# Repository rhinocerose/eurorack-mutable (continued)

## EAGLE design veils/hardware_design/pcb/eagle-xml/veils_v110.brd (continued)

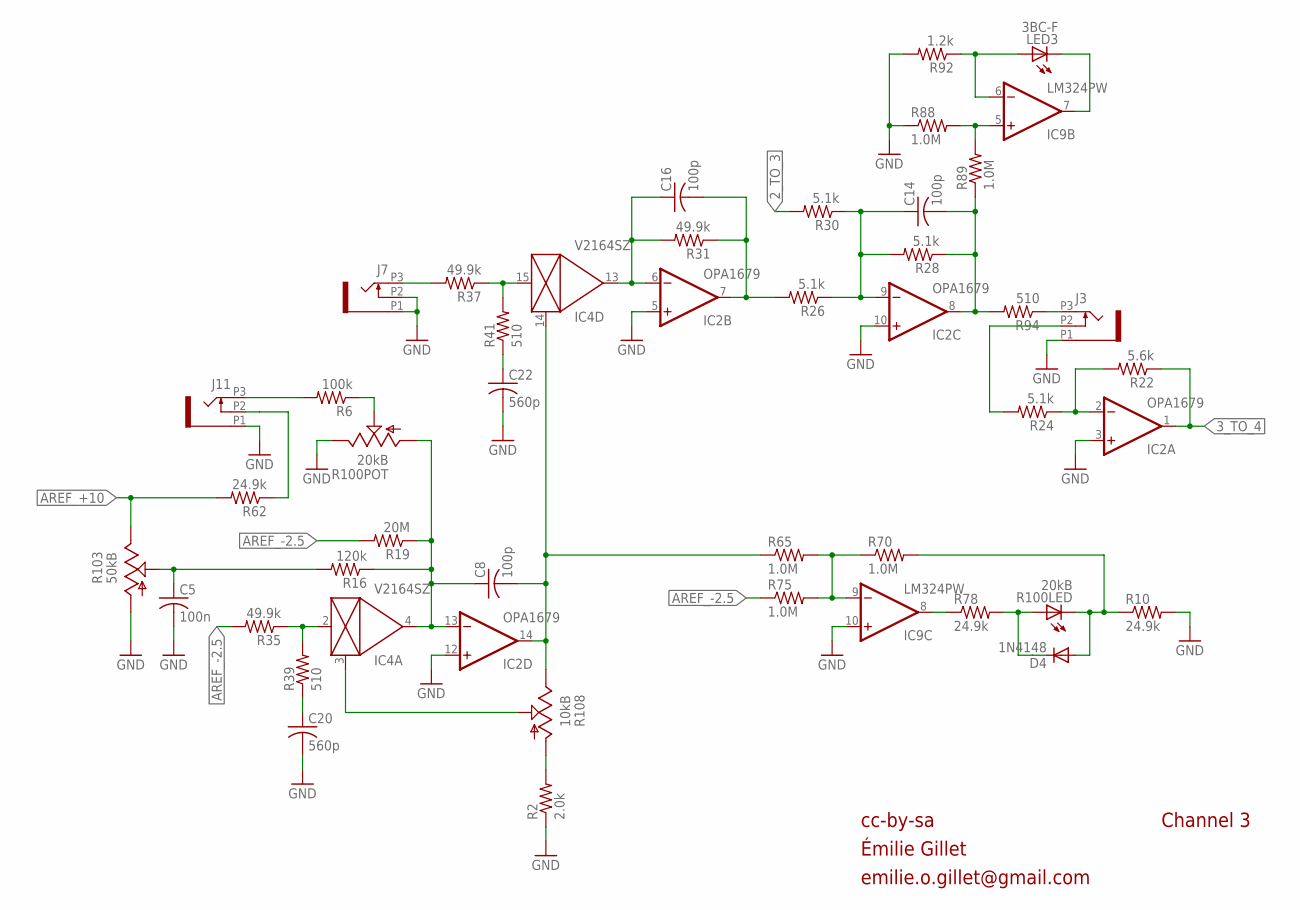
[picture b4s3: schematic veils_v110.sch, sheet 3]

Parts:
C5: 100n; C0402
C8, C14, C16: 100p; C0402
C20, C22: 560p; C0402
D4: 1N4148; SOD523
IC2: OPA1679; TSSOP14_065
IC4: V2164SZ; SOIC16N
IC9: LM324PW; TSSOP14_065
J3, J7, J11: PJ301_THONKICONNTME; WQP_PJ_301M_TME
LED3: 3BC-F; LED3MM
R2: 2.0k; R0402
R6: 100k; R0402
R10, R62, R78: 24.9k; R0402
R16: 120k; R0402
R19: 20M; R0402
R22: 5.6k; R0402
R24, R26, R28, R30: 5.1k; R0402
R31, R35, R37: 49.9k; R0402
R39, R41: 510; R0402
R65, R70, R75, R88, R89: 1.0M; R0402
R92: 1.2k; R0402
R94: 510; R0603
R100: 20kB; BOURNS_SLIDER
R103: 50kB; ALPS_POT_NARROW
R108: 10kB; ALPS_POT_NARROW

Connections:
2_TO_3: R30.2; also elsewhere on the board
3_TO_4: IC2.1 (OUT), R22.1; also elsewhere on the board
AREF_+10: R62.2, R103.P$1 (E); also elsewhere on the board
AREF_-2.5: R19.2, R35.2, R75.1; also elsewhere on the board
FOO2: IC4.2 (IN), R35.1, R39.2
GND: C5.2, C20.2, C22.2, IC2.3 (+IN), IC2.5 (+IN), IC2.10 (+IN), IC2.12 (+IN), IC9.10 (+IN), J3.P1 (1), J7.P1 (1), J7.P2 (2), J11.P1 (1), R2.1, R10.2, R88.1, R92.2, R100.3 (E), R103.P$3 (A); also elsewhere on the board
unnamed: IC9.5 (+IN), R88.2, R89.2
unnamed: J3.P3 (3), R94.1
unnamed: IC4.3 (CTRL), R108.P$2 (S)
unnamed: R2.2, R108.P$3 (A)
unnamed: J11.P3 (3), R6.2
unnamed: C22.1, R41.1
unnamed: IC4.15 (IN), R37.1, R41.2
unnamed: C14.1, IC2.9 (-IN), R26.1, R28.2, R30.1
unnamed: J7.P3 (3), R37.2
unnamed: C16.1, IC2.6 (-IN), IC4.13 (OUT), R31.2
unnamed: IC9.7 (OUT), LED3.K (C)
unnamed: IC9.6 (-IN), LED3.A, R92.1
unnamed: IC2.2 (-IN), R22.2, R24.1
unnamed: J3.P2 (2), R24.2
unnamed: C20.1, R39.1
unnamed: R6.1, R100.2 (S)
unnamed: C8.1, IC2.13 (-IN), IC4.4 (OUT), R16.1, R19.1, R100.1 (A)
unnamed: IC9.8 (OUT), R78.1
unnamed: D4.A, R10.1, R70.2, R100.E (C)
unnamed: IC9.9 (-IN), R65.2, R70.1, R75.2
unnamed: C8.2, IC2.14 (OUT), IC4.14 (CTRL), R65.1, R108.P$1 (E)
unnamed: J11.P2 (2), R62.1
unnamed: C5.1, R16.2, R103.P$2 (S)
unnamed: C16.2, IC2.7 (OUT), R26.2, R31.1
OUT3: C14.2, IC2.8 (OUT), R28.1, R89.1, R94.2
PROT3: D4.C, R78.2, R100.B (A)

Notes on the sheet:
cc-by-sa
Channel 3
Émilie Gillet
emilie.o.gillet@gmail.com

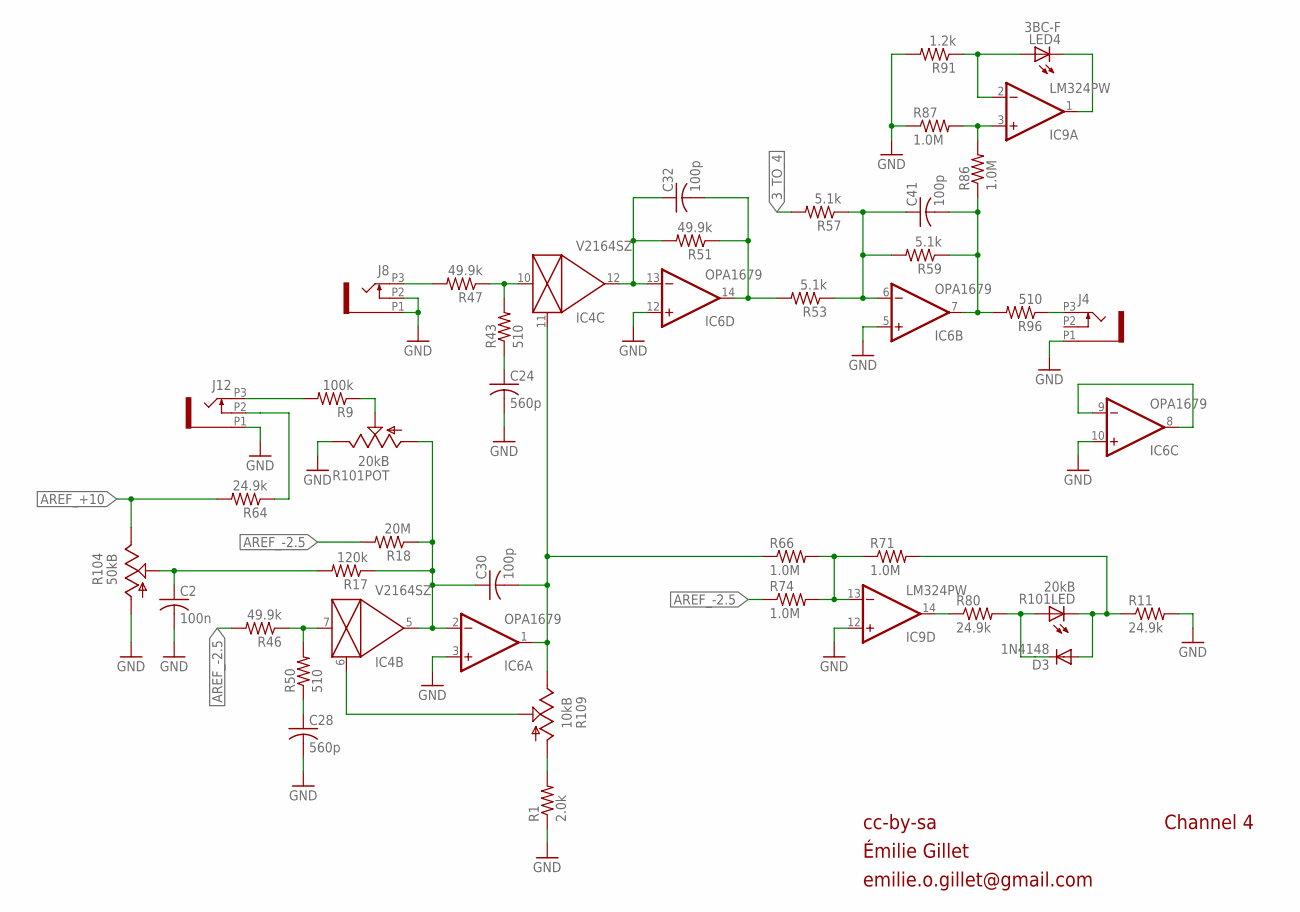
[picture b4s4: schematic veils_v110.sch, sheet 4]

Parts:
C2: 100n; C0402
C24, C28: 560p; C0402
C30, C32, C41: 100p; C0402
D3: 1N4148; SOD523
IC4: V2164SZ; SOIC16N
IC6: OPA1679; TSSOP14_065
IC9: LM324PW; TSSOP14_065
J4, J8, J12: PJ301_THONKICONNTME; WQP_PJ_301M_TME
LED4: 3BC-F; LED3MM
R1: 2.0k; R0402
R9: 100k; R0402
R11, R64, R80: 24.9k; R0402
R17: 120k; R0402
R18: 20M; R0402
R43, R50: 510; R0402
R46, R47, R51: 49.9k; R0402
R53, R57, R59: 5.1k; R0402
R66, R71, R74, R86, R87: 1.0M; R0402
R91: 1.2k; R0402
R96: 510; R0603
R101: 20kB; BOURNS_SLIDER
R104: 50kB; ALPS_POT_NARROW
R109: 10kB; ALPS_POT_NARROW

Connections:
3_TO_4: R57.2; also elsewhere on the board
AREF_+10: R64.2, R104.P$1 (E); also elsewhere on the board
AREF_-2.5: R18.2, R46.2, R74.1; also elsewhere on the board
FOO3: IC4.7 (IN), R46.1, R50.2
GND: C2.2, C24.2, C28.2, IC6.3 (+IN), IC6.5 (+IN), IC6.10 (+IN), IC6.12 (+IN), IC9.12 (+IN), J4.P1 (1), J8.P1 (1), J8.P2 (2), J12.P1 (1), R1.1, R11.2, R87.1, R91.2, R101.3 (E), R104.P$3 (A); also elsewhere on the board
unnamed: IC6.8 (OUT), IC6.9 (-IN)
unnamed: IC9.3 (+IN), R86.2, R87.2
unnamed: IC4.6 (CTRL), R109.P$2 (S)
unnamed: J12.P2 (2), R64.1
unnamed: R1.2, R109.P$3 (A)
unnamed: J12.P3 (3), R9.2
unnamed: C32.1, IC4.12 (OUT), IC6.13 (-IN), R51.2
unnamed: J8.P3 (3), R47.2
unnamed: R9.1, R101.2 (S)
unnamed: J4.P3 (3), R96.1
unnamed: C24.1, R43.1
unnamed: IC4.10 (IN), R43.2, R47.1
unnamed: C41.1, IC6.6 (-IN), R53.1, R57.1, R59.2
unnamed: IC9.1 (OUT), LED4.K (C)
unnamed: IC9.2 (-IN), LED4.A, R91.1
unnamed: IC9.14 (OUT), R80.1
unnamed: C32.2, IC6.14 (OUT), R51.1, R53.2
unnamed: C28.1, R50.1
unnamed: C30.1, IC4.5 (OUT), IC6.2 (-IN), R17.1, R18.1, R101.1 (A)
unnamed: D3.A, R11.1, R71.2, R101.E (C)
unnamed: IC9.13 (-IN), R66.2, R71.1, R74.2
unnamed: C30.2, IC4.11 (CTRL), IC6.1 (OUT), R66.1, R109.P$1 (E)
unnamed: C2.1, R17.2, R104.P$2 (S)
OUT4: C41.2, IC6.7 (OUT), R59.1, R86.1, R96.2
PROT4: D3.C, R80.2, R101.B (A)

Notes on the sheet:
cc-by-sa
Channel 4
Émilie Gillet
emilie.o.gillet@gmail.com

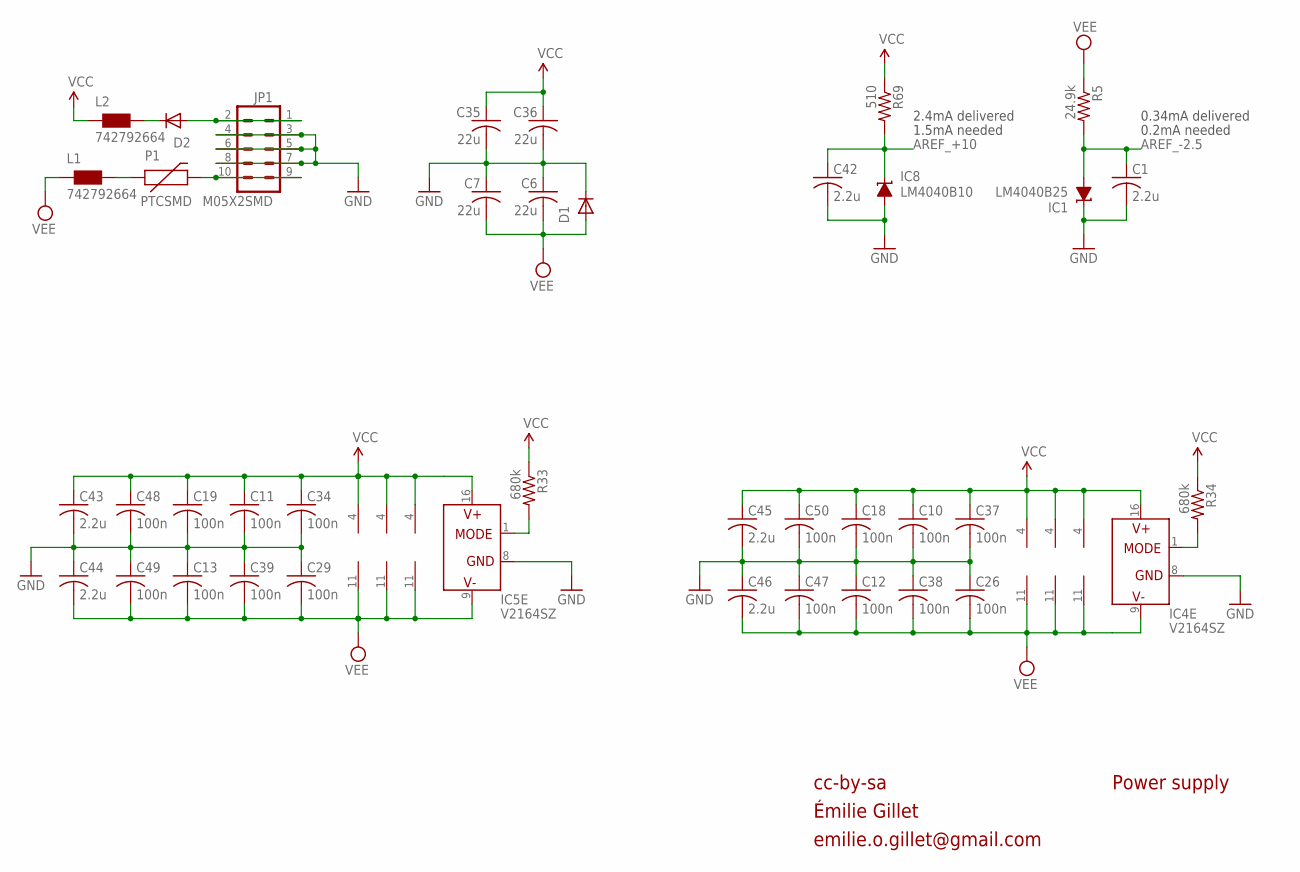
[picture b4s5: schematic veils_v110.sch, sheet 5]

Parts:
C1, C42, C43, C44, C45, C46: 2.2u; C0603
C6, C7, C35, C36: 22u; C1206
C10, C11, C12, C13, C18, C19, C26, C29, C34, C37, C38, C39, C47, C48, C49, C50: 100n; C0402
D1, D2: 1N5819HW; SOD123
IC1: LM4040B25; DBZ_R-PDSO-G3
IC2, IC3, IC6, IC7: OPA1679; TSSOP14_065
IC4, IC5: V2164SZ; SOIC16N
IC8: LM4040B10; DBZ_R-PDSO-G3
IC9, IC10: LM324PW; TSSOP14_065
JP1: M05X2SMD; 2X5-SMD
L1, L2: 742792664; 0603
P1: PTCSMD; PTC-1206
R5: 24.9k; R0402
R33, R34: 680k; R0402
R69: 510; R0402

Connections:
AREF_+10: C42.1, IC8.1 (C), R69.2; also elsewhere on the board
AREF_-2.5: C1.1, IC1.2 (A), R5.2; also elsewhere on the board
GND: C1.2, C6.1, C7.1, C10.2, C11.2, C12.1, C13.1, C18.2, C19.2, C26.1, C29.1, C34.2, C35.2, C36.2, C37.2, C38.1, C39.1, C42.2, C43.2, C44.1, C45.2, C46.1, C47.1, C48.2, C49.1, C50.2, D1.C, IC1.1 (C), IC4.8 (GND), IC5.8 (GND), IC8.2 (A), JP1.3, JP1.4, JP1.5, JP1.6, JP1.7, JP1.8; also elsewhere on the board
unnamed: D2.A, JP1.1, JP1.2
unnamed: JP1.9, JP1.10, P1.2
unnamed: L1.2, P1.1
unnamed: D2.C, L2.2
unnamed: IC5.1 (MODE), R33.2
unnamed: IC4.1 (MODE), R34.2
VCC: C10.1, C11.1, C18.1, C19.1, C34.1, C35.1, C36.1, C37.1, C43.1, C45.1, C48.1, C50.1, IC2.4 (V+), IC3.4 (V+), IC4.16 (V+), IC5.16 (V+), IC6.4 (V+), IC7.4 (V+), IC9.4 (V+), IC10.4 (V+), L2.1, R33.1, R34.1, R69.1
VEE: C6.2, C7.2, C12.2, C13.2, C26.2, C29.2, C38.2, C39.2, C44.2, C46.2, C47.2, C49.2, D1.A, IC2.11 (V-), IC3.11 (V-), IC4.9 (V-), IC5.9 (V-), IC6.11 (V-), IC7.11 (V-), IC9.11 (V-), IC10.11 (V-), L1.1, R5.1

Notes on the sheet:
cc-by-sa
Power supply
0.34mA delivered
2.4mA delivered
0.2mA needed
1.5mA needed
Émilie Gillet
emilie.o.gillet@gmail.com

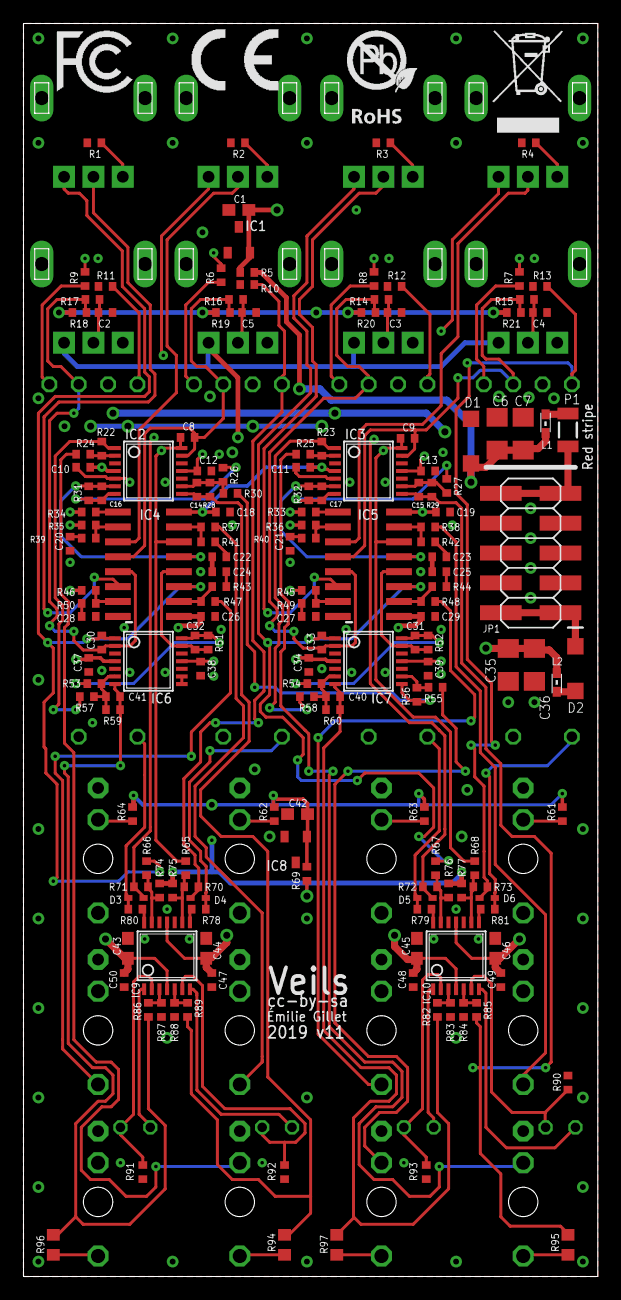
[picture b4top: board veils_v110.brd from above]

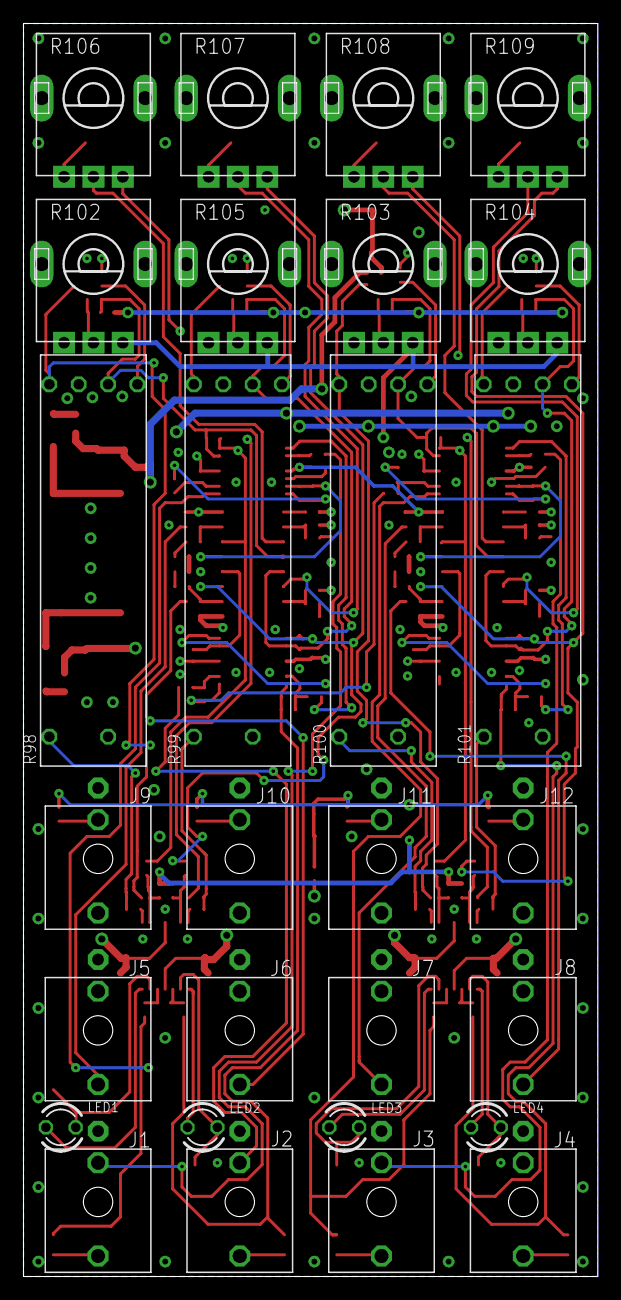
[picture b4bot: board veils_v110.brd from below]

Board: 4 copper layers, 48.9 x 106.7 mm, 199 parts (28 on the bottom side), 121 nets.

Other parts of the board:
U$1: CE_MEDIUM
U$2: FCC_MEDIUM
U$3: ROHS_LOGO
U$4: TRASHCAN_LOGO

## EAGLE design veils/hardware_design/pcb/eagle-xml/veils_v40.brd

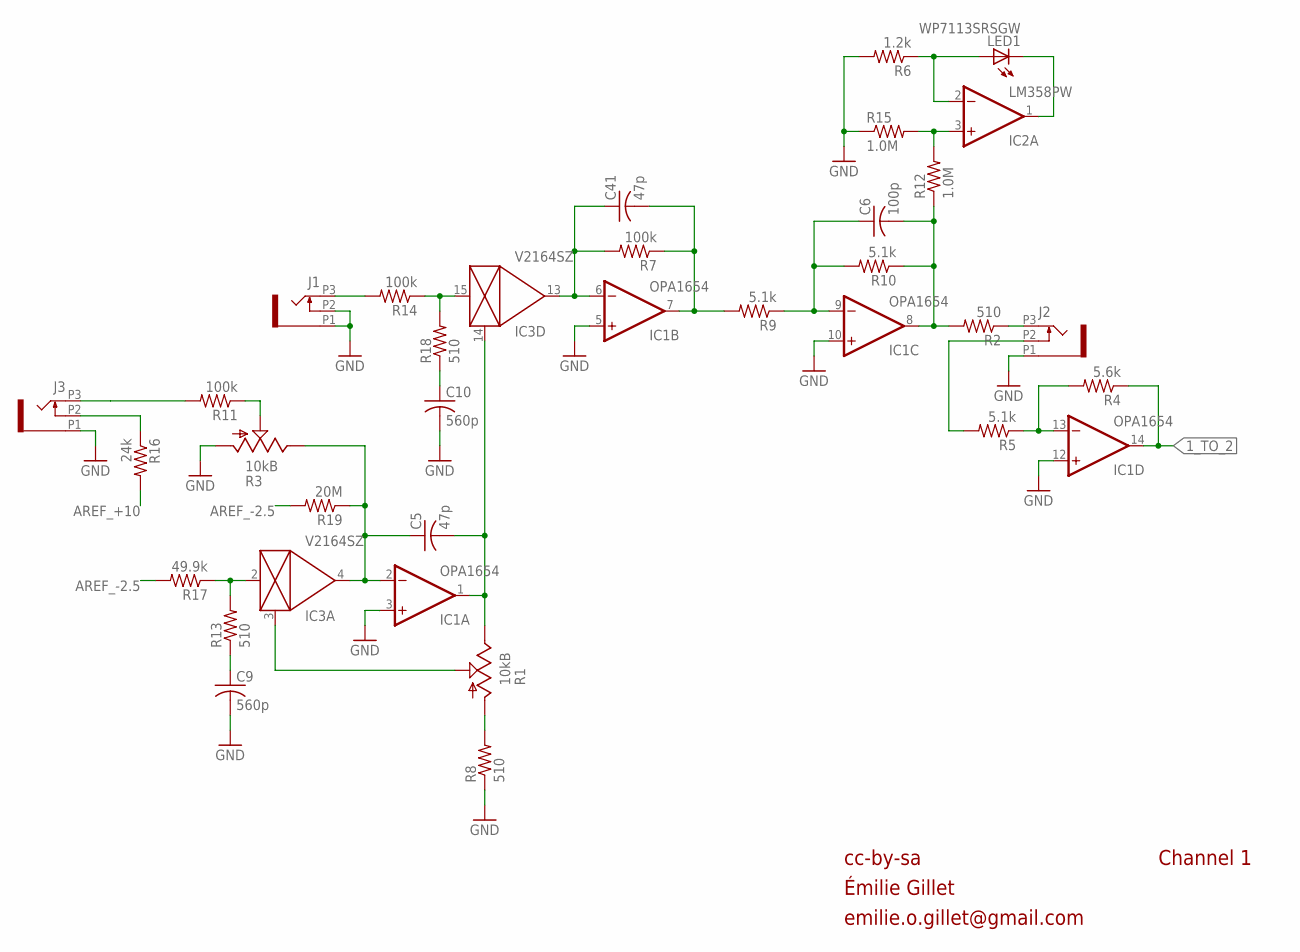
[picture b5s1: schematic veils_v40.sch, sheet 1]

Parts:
C5, C41: 47p; C0402
C6: 100p; C0402
C9, C10: 560p; C0402
IC1: OPA1654; TSSOP14
IC2: LM358PW; TSSOP8
IC3: V2164SZ; SOIC16N
J1, J2, J3: PJ301_THONKICONN6; WQP_PJ_301M6
LED1: WP7113SRSGW; LED5MM
R1: 10kB; ALPS_POT_VERTICAL
R2, R8, R13, R18: 510; R0402
R3: 10kB; ALPS_POT_VERTICAL_PS
R4: 5.6k; R0402
R5, R9, R10: 5.1k; R0402
R6: 1.2k; R0402
R7, R11, R14: 100k; R0402
R12, R15: 1.0M; R0402
R16: 24k; R0402
R17: 49.9k; R0402
R19: 20M; R0402

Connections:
1_TO_2: IC1.14 (OUT), R4.1; also elsewhere on the board
AREF_+10: R16.2; also elsewhere on the board
AREF_-2.5: R17.2, R19.2; also elsewhere on the board
CV_IN_1: J3.P3 (3), R11.2
FOO: IC3.2 (IN), R13.2, R17.1
GND: C9.2, C10.2, IC1.3 (+IN), IC1.5 (+IN), IC1.10 (+IN), IC1.12 (+IN), J1.P1 (1), J1.P2 (2), J2.P1 (1), J3.P1 (1), R3.P$3 (A), R6.2, R8.1, R15.1; also elsewhere on the board
unnamed: IC2.3 (+IN), R12.2, R15.2
unnamed: J2.P3 (3), R2.1
unnamed: IC3.3 (CTRL), R1.P$2 (S)
unnamed: C6.1, IC1.9 (-IN), R9.1, R10.2
unnamed: R3.P$2 (S), R11.1
unnamed: R1.P$3 (A), R8.2
unnamed: IC2.1 (OUT), LED1.K (C)
unnamed: IC2.2 (-IN), LED1.A, R6.1
unnamed: C9.1, R13.1
unnamed: J3.P2 (2), R16.1
unnamed: IC1.13 (-IN), R4.2, R5.1
unnamed: J2.P2 (2), R5.2
unnamed: C10.1, R18.1
unnamed: C5.1, IC1.2 (-IN), IC3.4 (OUT), R3.P$1 (E), R19.1
unnamed: J1.P3 (3), R14.2
unnamed: IC3.15 (IN), R14.1, R18.2
unnamed: C5.2, IC1.1 (OUT), IC3.14 (CTRL), R1.P$1 (E)
unnamed: C41.1, IC1.6 (-IN), IC3.13 (OUT), R7.2
unnamed: C41.2, IC1.7 (OUT), R7.1, R9.2
OUT1: C6.2, IC1.8 (OUT), R2.2, R10.1, R12.1

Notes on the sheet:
cc-by-sa
Channel 1
Émilie Gillet
emilie.o.gillet@gmail.com

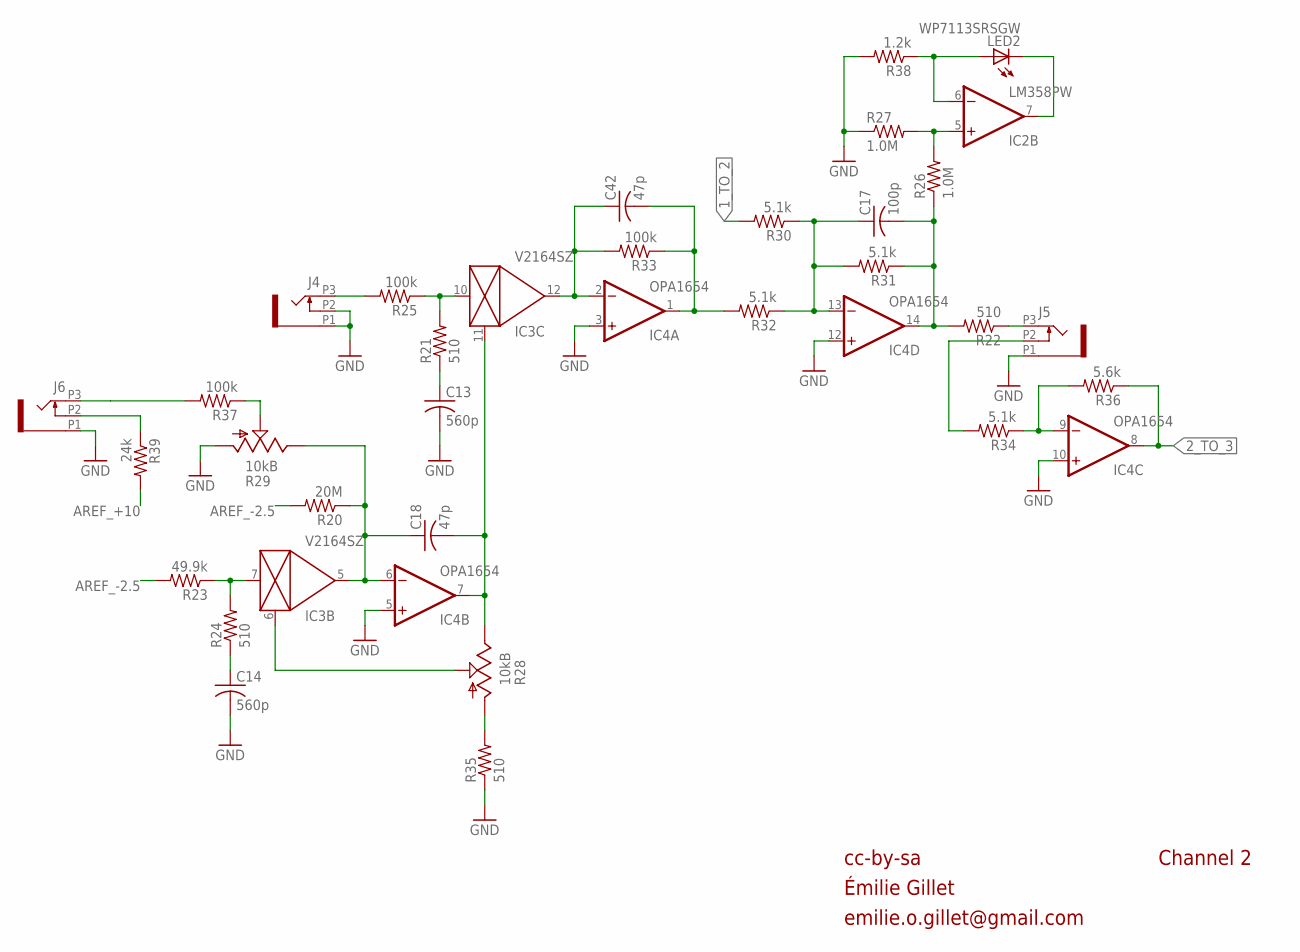
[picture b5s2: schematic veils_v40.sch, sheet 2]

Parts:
C13, C14: 560p; C0402
C17: 100p; C0402
C18, C42: 47p; C0402
IC2: LM358PW; TSSOP8
IC3: V2164SZ; SOIC16N
IC4: OPA1654; TSSOP14
J4, J5, J6: PJ301_THONKICONN6; WQP_PJ_301M6
LED2: WP7113SRSGW; LED5MM
R20: 20M; R0402
R21, R22, R24, R35: 510; R0402
R23: 49.9k; R0402
R25, R33, R37: 100k; R0402
R26, R27: 1.0M; R0402
R28: 10kB; ALPS_POT_VERTICAL
R29: 10kB; ALPS_POT_VERTICAL_PS
R30, R31, R32, R34: 5.1k; R0402
R36: 5.6k; R0402
R38: 1.2k; R0402
R39: 24k; R0402

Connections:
1_TO_2: R30.2; also elsewhere on the board
2_TO_3: IC4.8 (OUT), R36.1; also elsewhere on the board
AREF_+10: R39.2; also elsewhere on the board
AREF_-2.5: R20.2, R23.2; also elsewhere on the board
FOO1: IC3.7 (IN), R23.1, R24.2
GND: C13.2, C14.2, IC4.3 (+IN), IC4.5 (+IN), IC4.10 (+IN), IC4.12 (+IN), J4.P1 (1), J4.P2 (2), J5.P1 (1), J6.P1 (1), R27.1, R29.P$3 (A), R35.1, R38.2; also elsewhere on the board
unnamed: J4.P3 (3), R25.2
unnamed: IC2.5 (+IN), R26.2, R27.2
unnamed: J5.P3 (3), R22.1
unnamed: C13.1, R21.1
unnamed: IC3.10 (IN), R21.2, R25.1
unnamed: IC3.6 (CTRL), R28.P$2 (S)
unnamed: C17.1, IC4.13 (-IN), R30.1, R31.2, R32.1
unnamed: C18.2, IC3.11 (CTRL), IC4.7 (OUT), R28.P$1 (E)
unnamed: R28.P$3 (A), R35.2
unnamed: IC2.7 (OUT), LED2.K (C)
unnamed: IC2.6 (-IN), LED2.A, R38.1
unnamed: IC4.9 (-IN), R34.1, R36.2
unnamed: J5.P2 (2), R34.2
unnamed: C42.2, IC4.1 (OUT), R32.2, R33.1
unnamed: R29.P$2 (S), R37.1
unnamed: C14.1, R24.1
unnamed: C18.1, IC3.5 (OUT), IC4.6 (-IN), R20.1, R29.P$1 (E)
unnamed: J6.P3 (3), R37.2
unnamed: C42.1, IC3.12 (OUT), IC4.2 (-IN), R33.2
unnamed: J6.P2 (2), R39.1
OUT2: C17.2, IC4.14 (OUT), R22.2, R26.1, R31.1

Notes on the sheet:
cc-by-sa
Channel 2
Émilie Gillet
emilie.o.gillet@gmail.com

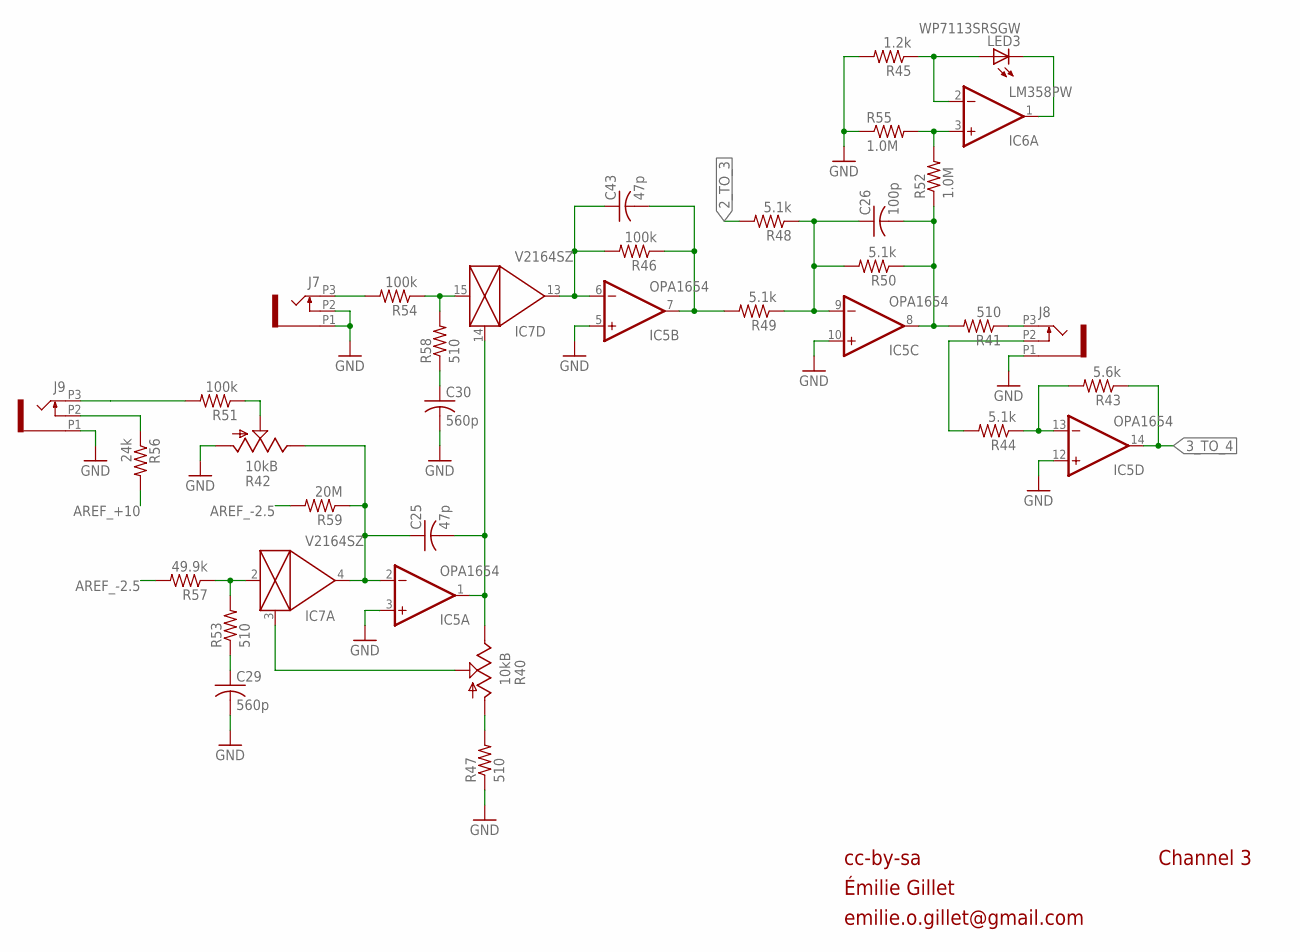
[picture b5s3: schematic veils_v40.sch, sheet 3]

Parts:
C25, C43: 47p; C0402
C26: 100p; C0402
C29, C30: 560p; C0402
IC5: OPA1654; TSSOP14
IC6: LM358PW; TSSOP8
IC7: V2164SZ; SOIC16N
J7, J8, J9: PJ301_THONKICONN6; WQP_PJ_301M6
LED3: WP7113SRSGW; LED5MM
R40: 10kB; ALPS_POT_VERTICAL
R41, R47, R53, R58: 510; R0402
R42: 10kB; ALPS_POT_VERTICAL_PS
R43: 5.6k; R0402
R44, R48, R49, R50: 5.1k; R0402
R45: 1.2k; R0402
R46, R51, R54: 100k; R0402
R52, R55: 1.0M; R0402
R56: 24k; R0402
R57: 49.9k; R0402
R59: 20M; R0402

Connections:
2_TO_3: R48.2; also elsewhere on the board
3_TO_4: IC5.14 (OUT), R43.1; also elsewhere on the board
AREF_+10: R56.2; also elsewhere on the board
AREF_-2.5: R57.2, R59.2; also elsewhere on the board
FOO2: IC7.2 (IN), R53.2, R57.1
GND: C29.2, C30.2, IC5.3 (+IN), IC5.5 (+IN), IC5.10 (+IN), IC5.12 (+IN), J7.P1 (1), J7.P2 (2), J8.P1 (1), J9.P1 (1), R42.P$3 (A), R45.2, R47.1, R55.1; also elsewhere on the board
unnamed: IC6.3 (+IN), R52.2, R55.2
unnamed: J8.P3 (3), R41.1
unnamed: IC7.3 (CTRL), R40.P$2 (S)
unnamed: C25.2, IC5.1 (OUT), IC7.14 (CTRL), R40.P$1 (E)
unnamed: R40.P$3 (A), R47.2
unnamed: C30.1, R58.1
unnamed: IC7.15 (IN), R54.1, R58.2
unnamed: C26.1, IC5.9 (-IN), R48.1, R49.1, R50.2
unnamed: J9.P2 (2), R56.1
unnamed: J7.P3 (3), R54.2
unnamed: J9.P3 (3), R51.2
unnamed: C43.1, IC5.6 (-IN), IC7.13 (OUT), R46.2
unnamed: IC6.1 (OUT), LED3.K (C)
unnamed: IC6.2 (-IN), LED3.A, R45.1
unnamed: IC5.13 (-IN), R43.2, R44.1
unnamed: J8.P2 (2), R44.2
unnamed: C29.1, R53.1
unnamed: C25.1, IC5.2 (-IN), IC7.4 (OUT), R42.P$1 (E), R59.1
unnamed: R42.P$2 (S), R51.1
unnamed: C43.2, IC5.7 (OUT), R46.1, R49.2
OUT3: C26.2, IC5.8 (OUT), R41.2, R50.1, R52.1

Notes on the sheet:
cc-by-sa
Channel 3
Émilie Gillet
emilie.o.gillet@gmail.com

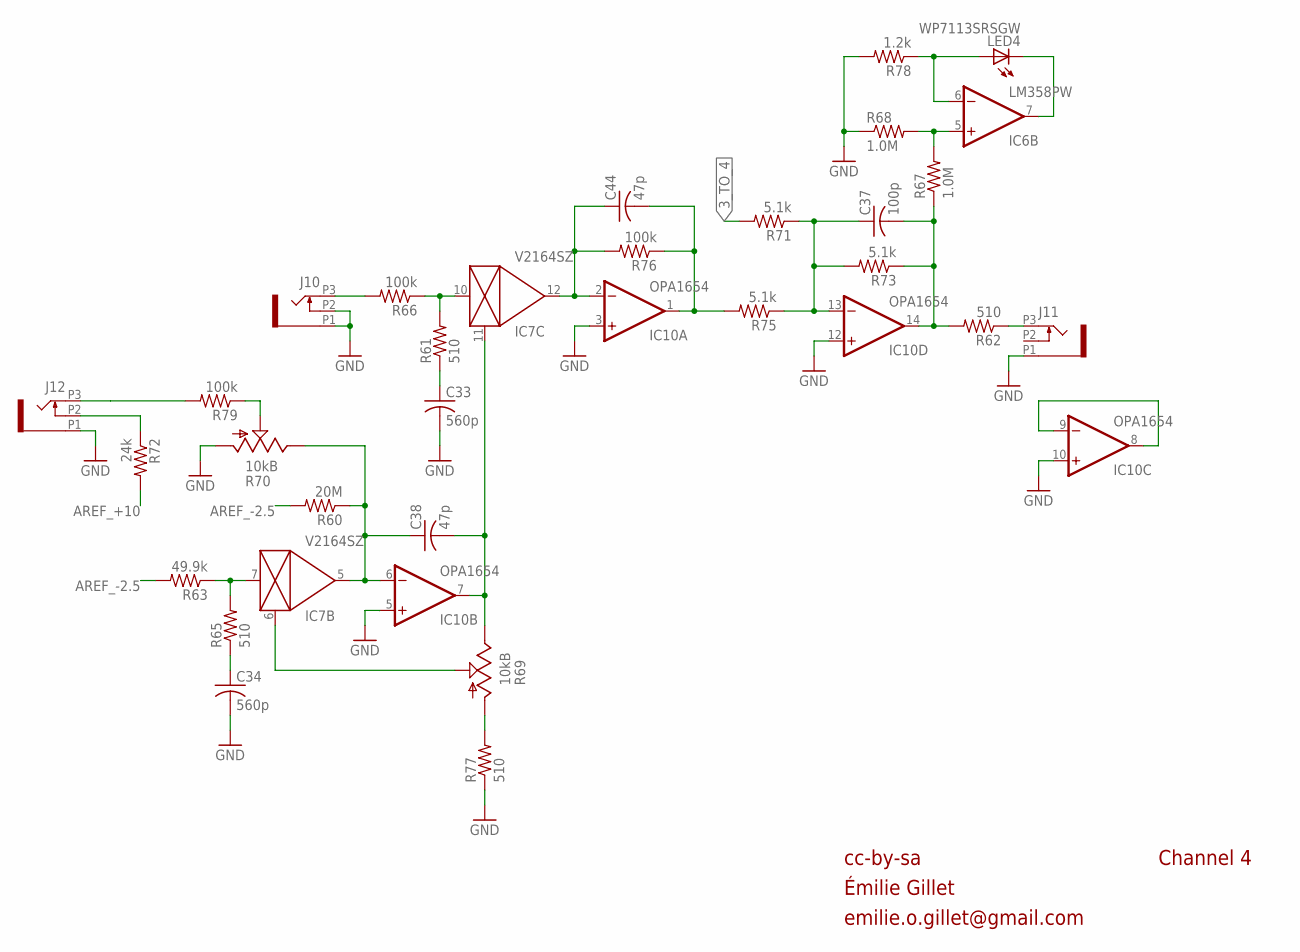
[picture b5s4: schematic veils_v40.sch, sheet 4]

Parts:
C33, C34: 560p; C0402
C37: 100p; C0402
C38, C44: 47p; C0402
IC6: LM358PW; TSSOP8
IC7: V2164SZ; SOIC16N
IC10: OPA1654; TSSOP14
J10, J11, J12: PJ301_THONKICONN6; WQP_PJ_301M6
LED4: WP7113SRSGW; LED5MM
R60: 20M; R0402
R61, R62, R65, R77: 510; R0402
R63: 49.9k; R0402
R66, R76, R79: 100k; R0402
R67, R68: 1.0M; R0402
R69: 10kB; ALPS_POT_VERTICAL
R70: 10kB; ALPS_POT_VERTICAL_PS
R71, R73, R75: 5.1k; R0402
R72: 24k; R0402
R78: 1.2k; R0402

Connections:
3_TO_4: R71.2; also elsewhere on the board
AREF_+10: R72.2; also elsewhere on the board
AREF_-2.5: R60.2, R63.2; also elsewhere on the board
FOO3: IC7.7 (IN), R63.1, R65.2
GND: C33.2, C34.2, IC10.3 (+IN), IC10.5 (+IN), IC10.10 (+IN), IC10.12 (+IN), J10.P1 (1), J10.P2 (2), J11.P1 (1), J12.P1 (1), R68.1, R70.P$3 (A), R77.1, R78.2; also elsewhere on the board
unnamed: IC10.8 (OUT), IC10.9 (-IN)
unnamed: IC6.5 (+IN), R67.2, R68.2
unnamed: C38.2, IC7.11 (CTRL), IC10.7 (OUT), R69.P$1 (E)
unnamed: IC7.6 (CTRL), R69.P$2 (S)
unnamed: R69.P$3 (A), R77.2
unnamed: C44.1, IC7.12 (OUT), IC10.2 (-IN), R76.2
unnamed: J10.P3 (3), R66.2
unnamed: J11.P3 (3), R62.1
unnamed: C33.1, R61.1
unnamed: IC7.10 (IN), R61.2, R66.1
unnamed: C37.1, IC10.13 (-IN), R71.1, R73.2, R75.1
unnamed: J12.P3 (3), R79.2
unnamed: IC6.7 (OUT), LED4.K (C)
unnamed: IC6.6 (-IN), LED4.A, R78.1
unnamed: C44.2, IC10.1 (OUT), R75.2, R76.1
unnamed: R70.P$2 (S), R79.1
unnamed: C34.1, R65.1
unnamed: C38.1, IC7.5 (OUT), IC10.6 (-IN), R60.1, R70.P$1 (E)
unnamed: J12.P2 (2), R72.1
OUT4: C37.2, IC10.14 (OUT), R62.2, R67.1, R73.1

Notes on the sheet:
cc-by-sa
Channel 4
Émilie Gillet
emilie.o.gillet@gmail.com

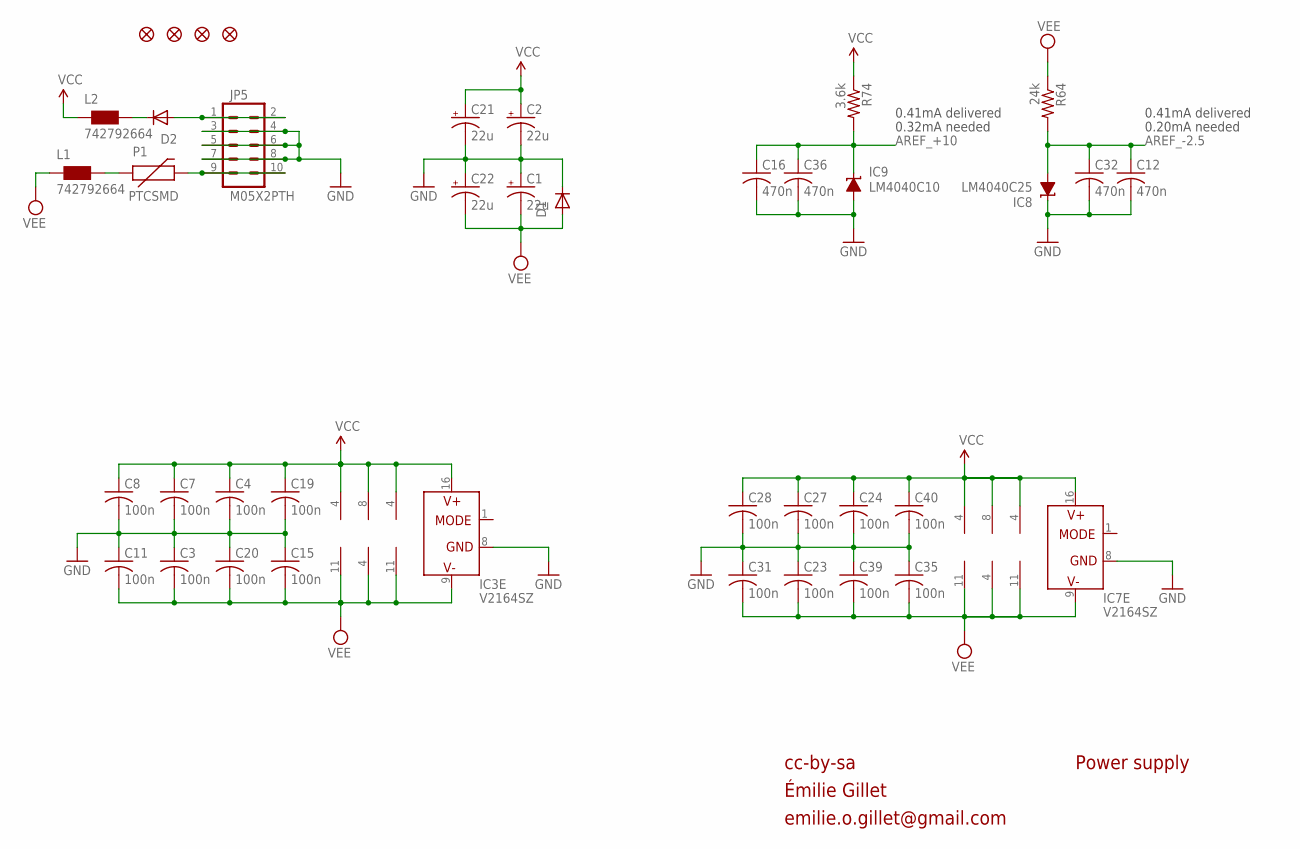
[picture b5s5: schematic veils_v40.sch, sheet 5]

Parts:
C1, C2, C21, C22: 22u; PANASONIC_B
C3, C4, C7, C8, C11, C15, C19, C20, C23, C24, C27, C28, C31, C35, C39, C40: 100n; C0402
C12, C16, C32, C36: 470n; C0402
D1, D2: 1N5819HW; SOD123
IC1, IC4, IC5, IC10: OPA1654; TSSOP14
IC2, IC6: LM358PW; TSSOP8
IC3, IC7: V2164SZ; SOIC16N
IC8: LM4040C25; DBZ_R-PDSO-G3
IC9: LM4040C10; DBZ_R-PDSO-G3
JP1, JP2, JP3, JP4: FIDUCIAL1X2; FIDUCIAL-1X2
JP5: M05X2PTH; AVR_ICSP
L1, L2: 742792664; 0603
P1: PTCSMD; PTC-1206
R64: 24k; R0402
R74: 3.6k; R0402

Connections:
AREF_+10: C16.1, C36.1, IC9.1 (C), R74.2; also elsewhere on the board
AREF_-2.5: C12.1, C32.1, IC8.2 (A), R64.2; also elsewhere on the board
GND: C1.+, C2.-, C3.1, C4.2, C7.2, C8.2, C11.1, C12.2, C15.1, C16.2, C19.2, C20.1, C21.-, C22.+, C23.1, C24.2, C27.2, C28.2, C31.1, C32.2, C35.1, C36.2, C39.1, C40.2, D1.C, IC3.8 (GND), IC7.8 (GND), IC8.1 (C), IC9.2 (A), JP5.3, JP5.4, JP5.5, JP5.6, JP5.7, JP5.8; also elsewhere on the board
unnamed: D2.A, JP5.1, JP5.2
unnamed: JP5.9, JP5.10, P1.2
unnamed: L1.2, P1.1
unnamed: D2.C, L2.2
VCC: C2.+, C4.1, C7.1, C8.1, C19.1, C21.+, C24.1, C27.1, C28.1, C40.1, IC1.4 (V+), IC2.8 (V+), IC3.16 (V+), IC4.4 (V+), IC5.4 (V+), IC6.8 (V+), IC7.16 (V+), IC10.4 (V+), L2.1, R74.1
VEE: C1.-, C3.2, C11.2, C15.2, C20.2, C22.-, C23.2, C31.2, C35.2, C39.2, D1.A, IC1.11 (V-), IC2.4 (V-), IC3.9 (V-), IC4.11 (V-), IC5.11 (V-), IC6.4 (V-), IC7.9 (V-), IC10.11 (V-), L1.1, R64.1

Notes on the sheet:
cc-by-sa
Power supply
0.41mA delivered
0.20mA needed
0.32mA needed
Émilie Gillet
emilie.o.gillet@gmail.com

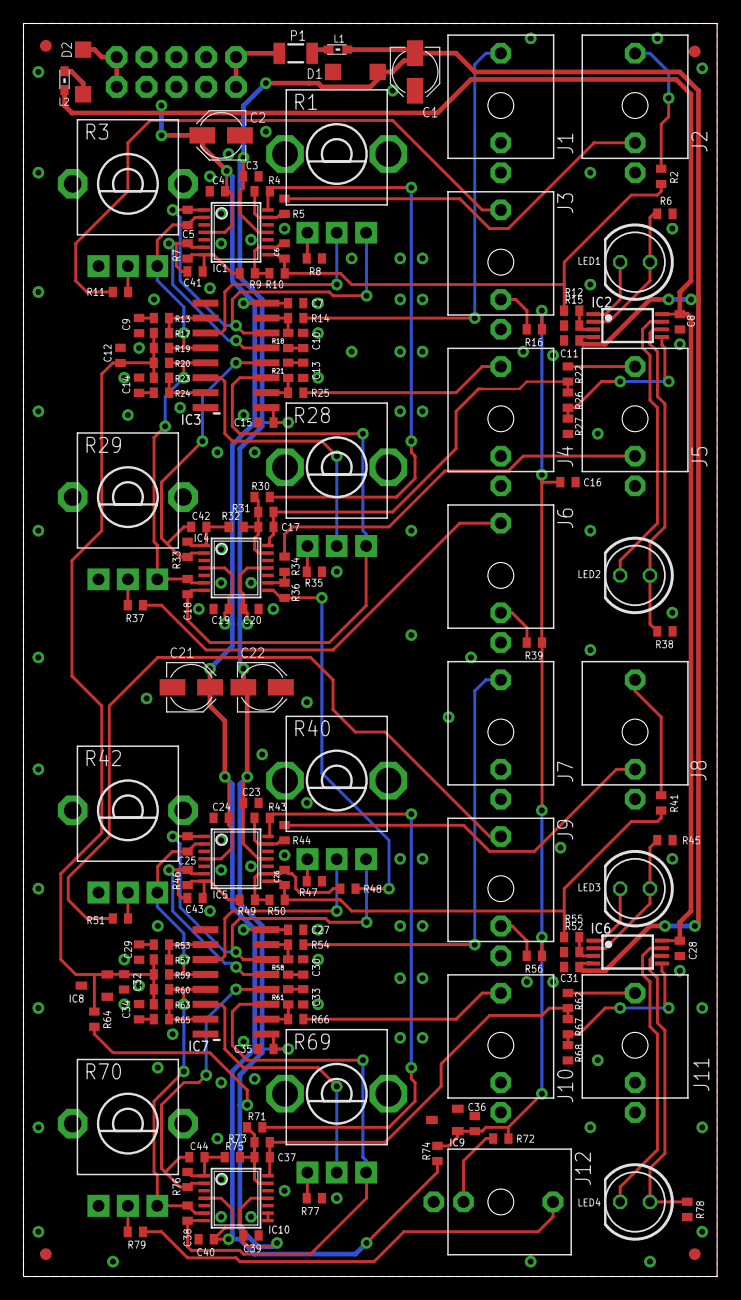
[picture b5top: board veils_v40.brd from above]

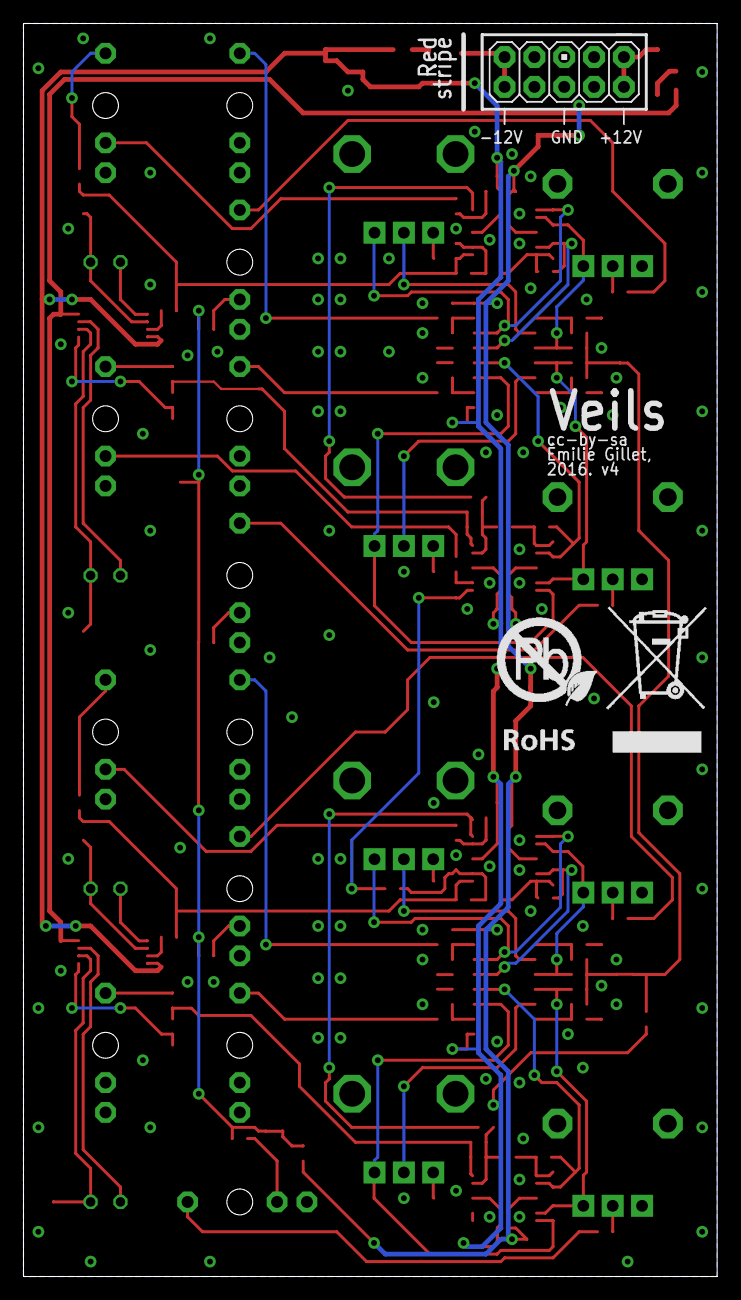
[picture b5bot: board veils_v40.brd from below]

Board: 2 copper layers, 59.1 x 106.7 mm, 160 parts (2 on the bottom side), 99 nets.

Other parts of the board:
U$2: ROHS_BIG
